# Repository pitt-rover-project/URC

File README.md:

# 🚀 University Rover Challenge - Pitt Robotics

> **Advanced Autonomous Rover System for University Rover Challenge**
> *ROS 2 • Python • Arduino • Docker • Computer Vision*

## 🎯 Project Overview

Complete software stack for the **University of Pittsburgh's University Rover Challenge (URC) Rover**. This system integrates advanced robotics technologies to compete in one of the most prestigious collegiate robotics competitions.

### 🏆 Competition Tasks
- **🚶 Autonomous Navigation** - GPS-guided traversal of challenging terrain
- **🎯 Equipment Servicing** - Precise manipulation tasks with robotic arm
- **📦 Extreme Delivery** - Package delivery in harsh environments
- **🔬 Science Operations** - Sample collection and analysis
- **🕹️ Teleoperation** - Manual control for complex scenarios

## ⚡ Quick Start

### 🐳 Docker Setup (Recommended)

**macOS Development:**
```bash
cd docker/local
chmod +x start_mac.sh
./start_mac.sh
```

**Jetson/Linux Deployment:**
```bash
cd docker/jetson
chmod +x start.sh
./start.sh
```

**Simulation Mode:**
```bash
cd docker/local
./sim-launch.sh
```

### 🤖 Launch Rover System

```bash
# Start main control interface
python3 -m guis.gen_gui

# Launch specific subsystems
python3 -m guis.arduino_gui      # Hardware communication
python3 -m guis.auto_gui         # Autonomous navigation
python3 -m guis.equip_serv_gui   # Equipment servicing
```

## 🏗️ System Architecture

### **Core Components**

```
🌐 ROS 2 Network Layer
├── 📡 Sensor Bridges (GPS, IMU, Cameras)
├── 🎮 Control Interfaces (Teleop, Autonomous)
├── 🤖 Hardware Abstraction (Motors, Servos)
└── 📊 Data Processing (Computer Vision, Navigation)

🖥️ GUI Control System
├── 🎛️ General Control Dashboard
├── 🚗 Motor Control Interface
├── 🧭 Navigation & Mapping
└── 📸 Camera Feed Management

🔧 Hardware Integration
├── ⚡ Arduino Communication
├── 📶 Serial Protocol Bridges
├── 🎯 Motor Control Systems
└── 📡 Sensor Data Acquisition
```

## 🛠️ Development Workflow

### **ROS 2 Development**

```bash
# Build ROS workspace
cd simulation/colcon_ws
colcon build

# Launch robot simulation
ros2 launch my_robot_description display.launch.py use_sim_time:=true

# Control with keyboard
ros2 run teleop_twist_keyboard teleop_twist_keyboard --ros-args -r /cmd_vel:=/teleop_cmd_vel

# Monitor system status
ros2 run rqt_console rqt_console
```

### **Git Workflow**
```bash
# Create feature branch
git fetch
git checkout -b feature/your-improvement

# Development cycle
git add .
git commit -m "feat: add autonomous navigation improvements"
git push origin feature/your-improvement

# Create pull request for review
```

## 📊 Technology Stack

### **🤖 Robotics & Control**
- **ROS 2 Humble** - Robot operating system
- **Gazebo** - Physics simulation environment
- **OpenCV** - Computer vision processing
- **PyQt5** - GUI framework for control interfaces

### **🔧 Hardware Integration**
- **Arduino** - Embedded sensor/actuator control
- **Serial Communication** - Hardware abstraction layer
- **NVIDIA Jetson** - Edge computing platform
- **GPS/IMU Sensors** - Navigation and localization

### **🚀 DevOps & Deployment**
- **Docker** - Containerized development environment
- **Docker Compose** - Multi-service orchestration
- **Make** - Build automation and cleanup

## 🎮 Competition Features

### **🧠 Autonomous Navigation**
- GPS-waypoint following
- Obstacle detection and avoidance
- Terrain analysis and path planning
- Real-time localization and mapping

### **🎯 Precision Control**
- Robotic arm manipulation
- Equipment servicing protocols
- Sample collection automation
- Fine motor control systems

### **📡 Communication Systems**
- Long-range telemetry
- Video streaming capabilities
- Emergency stop protocols
- Multi-operator interface support

## 📈 Performance Metrics

- **Navigation Accuracy**: ±2m GPS positioning
- **Video Latency**: <200ms streaming
- **Control Response**: <50ms command execution
- **Battery Life**: 4+ hours autonomous operation
- **Operating Range**: 1km+ radio communication

## 🔍 Diagnostics & Monitoring

```bash
# System health check
./ros2_quick_diagnostic.sh

# Network connectivity
./udp_connectivity_test.py

# Hardware status
python3 guis/gen_gui.py  # View sensor dashboard

# Log analysis
tail -f *.log
```

---

**Team**: University of Pittsburgh Robotics Club
**Status**: Active Development - 2025 Season

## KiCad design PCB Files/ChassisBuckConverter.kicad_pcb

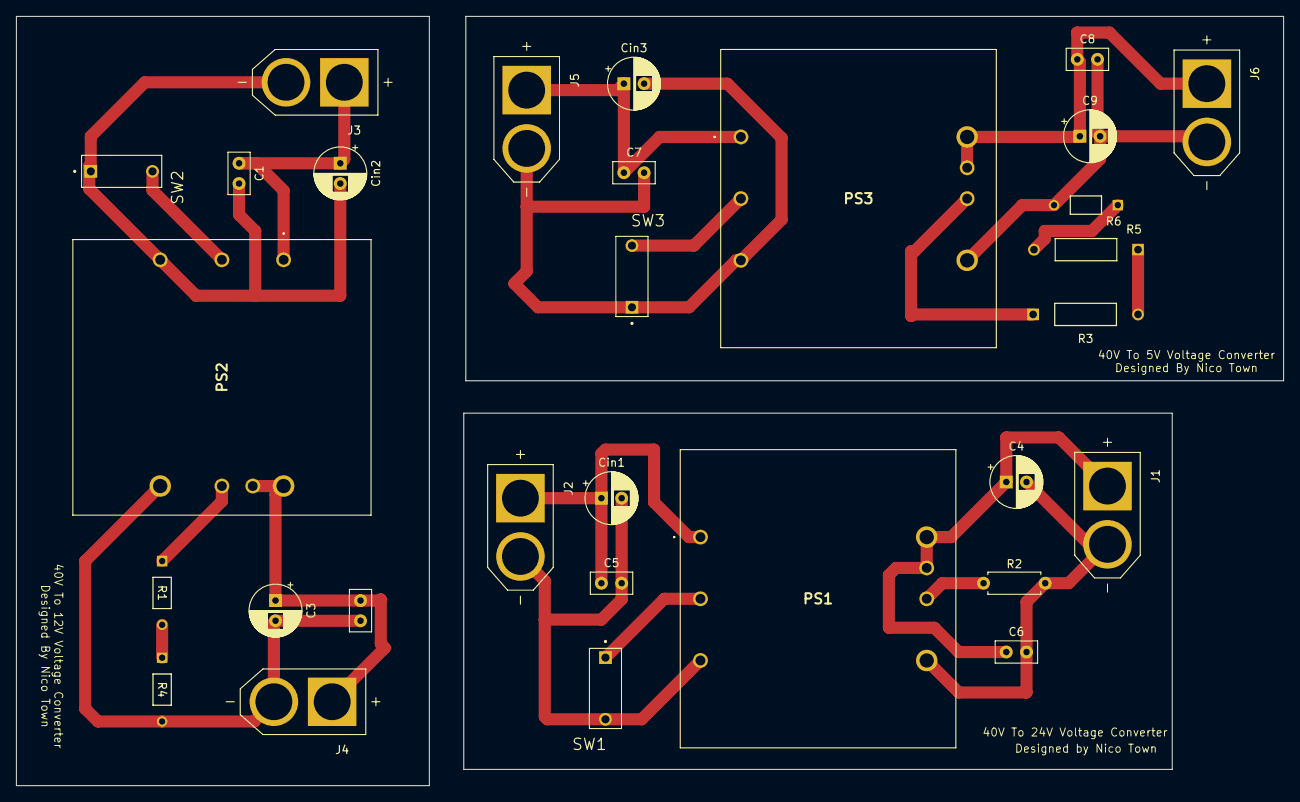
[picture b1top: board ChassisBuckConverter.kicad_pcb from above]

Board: 2 copper layers, 156.5 x 95.0 mm, 30 parts (0 on the bottom side), 21 nets.

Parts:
C1, C2, C5, C6, C7, C8: 22uF; C_Disc_D5.0mm_W2.5mm_P2.50mm
C3, C4, C9: 330uF; CP_Radial_D6.3mm_P2.50mm
Cin1, Cin2, Cin3: 330uF; CP_Radial_D6.3mm_P2.50mm
J1: 24V; AMASS_XT60-M
J2, J3, J5: 40V; AMASS_XT60-M
J4: 12V; AMASS_XT60-M
J6: 5V; AMASS_XT60-M
PS1, PS2, PS3: I7A48020A033V-0F1-R; I7A4W033A033V0F1R
R1: 1000; STA_CF18_STP
R2: 280; R_Axial_DIN0207_L6.3mm_D2.5mm_P7.62mm_Horizontal
R3: 8200; RES_CMF07_VIS
R4: 130; STA_CF18_STP
R5: 400; CMF55_VIS
R6: 180; STA_CF18_STP
SW1, SW2, SW3: SWITCH; SW_DS01-254-L-01BE

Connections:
unnamed: C4.2, C6.2, J1.N, PS1.4 (VOUT(-)), R2.2
unnamed: C4.1, C6.1, J1.P, PS1.7 (SENSE(+)), PS1.8 (VOUT(+))
unnamed: C5.1, Cin1.1, J2.P, PS1.1 (VIN(+))
unnamed: C5.2, Cin1.2, J2.N, PS1.3 (VIN(-)), SW1.1B
unnamed: C1.1, Cin2.1, J3.P, PS2.1 (VIN(+))
unnamed: C1.2, Cin2.2, J3.N, PS2.3 (VIN(-)), SW2.1A
unnamed: C2.2, C3.2, J4.N, PS2.4 (VOUT(-)), R4.2
unnamed: C2.1, C3.1, J4.P, PS2.7 (SENSE(+)), PS2.8 (VOUT(+))
unnamed: C7.1, Cin3.1, J5.P, PS3.1 (VIN(+))
unnamed: C7.2, Cin3.2, J5.N, PS3.3 (VIN(-)), SW3.1A
unnamed: C8.2, C9.2, J6.N, PS3.4 (VOUT(-)), R6.2
unnamed: C8.1, C9.1, J6.P, PS3.7 (SENSE(+)), PS3.8 (VOUT(+))
unnamed: PS1.2 (ON/OFF), SW1.1A
unnamed: PS1.6 (TRIM), R2.1
unnamed: PS2.2 (ON/OFF), SW2.1B
unnamed: PS2.6 (TRIM), R1.1
unnamed: PS3.2 (ON/OFF), SW3.1B
unnamed: PS3.6 (TRIM), R3.1
unnamed: R1.2, R4.1
unnamed: R3.2, R5.1
unnamed: R5.2, R6.1

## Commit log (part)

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2024-12-27 added current arduino code for gps, drive train, and ultrasonic sensors with their corresponding bridges
2024-12-27 fixed some issues with previous commit
2024-12-28 finished a basic docker set up
2024-12-28 combined the terminal publisher with the driver ros architecture
2024-12-31 start scripts
2024-12-31 subprocesses for the guis
2024-12-31 github cleanup
2025-01-09 updated port
2025-01-10 dockerfile fix
2025-01-10 updated pins
2025-01-10 ultrasonic fix
2025-01-13 docker readme
2025-01-13 better docker readme
2025-01-13 realsense for docker
2025-01-13 removed realsense
2025-01-13 docker attempt 2
2025-01-13 forgot -y
2025-01-13 docker attempt 3
2025-01-24 fixed a gui script
2025-01-25 docker attmpt 4
2025-01-25 docker compose
2025-01-25 commented out arduino for now
2025-01-25 removed acm0 for now
2025-01-25 privileged
2025-01-25 Created ime_demo arduino script
2025-01-25 docker for local
2025-01-27 added readme + fixed gui
2025-02-04 I say mama mia .py
2025-02-09 fixed some bridge code errors
2025-02-10 added teleop control to docker
2025-02-10 updated simulation
2025-02-10 deleted colcon_ws
2025-02-10 added colcon_ws to simulation
2025-02-10 removed colcon
2025-02-15 New files for simulation
2025-02-15 new motor stuff
2025-02-15 start up for the cameras
2025-02-15 Create Twist keyboard messages
2025-02-15 added distance between left and right wheels
2025-02-15 Making Gui code more Pythonic
2025-02-15 Added distance file
2025-02-15 Pushing branch to remote
2025-02-15 Adding the imu bridge
2025-02-17 Create Commands for Robot Subscriber
2025-02-18 Bridge work
2025-03-10 edited controls
2025-03-10 python3
2025-03-10 Fixing commented code - deletion
2025-03-10 Fixing even more! Commented out code.
2025-03-16 docker
2025-03-16 forgot an s
2025-03-16 Uploading progress on subscriber.py
2025-03-16 added a command
2025-03-16 Creating IMU Data Parser class that parses incoming message (from subscriber)
2025-03-16 Implementing feedback from Alexander's code review: "what the hell is the zip function? Use something simpler"
2025-03-22 testing 1st commit
2025-03-22 Added satellite parsing
2025-03-22 Added satellites parsing, changed distance prints, and motor serial
2025-04-07 Pushing latest work on subscribers - April 7th
2025-04-07 Connecting parsing interface with the subcriber hierarchy.
2025-04-08 Working on integrating GPS subscriber into the program. Fixing problems in arudino bridge base of missing motor code.
2025-04-12 mount drive into docker yaml
2025-04-12 camera file change
2025-04-12 Added more subscribers and teleop related matter. Fixed some spelling errors
2025-04-14 added hello.txt
2025-04-14 added hello.txt to branch alexiskwasinski
2025-04-14 reverting changes
2025-04-15 Fixed inaccurate baud rate. Back to 115200
2025-04-15 Resolving merge conflict - fixing error with version/volume keyword (volume accurate) in docker-compose.yml
2025-04-15 Resolving merge conflict.
2025-04-15 Working on integrating GPS subscriber into the program. Fixing problems in arudino bridge base of missing motor code.
    Resolving merge conflict...
2025-04-15 Resolving merge conflict
2025-04-19 Deleting build directory and adding instructions to README to run GUIs.
2025-04-19 changed the gui from rows/columns to cords and made it fullscreen
2025-06-02 Adding pycache to gitignore
2025-06-04 work on linking subscribers to gui
2025-06-17 Updates to docker/local documentation and testing subscribers in gui in local docker RLCPY [it works! I'm 90% sure]
2025-06-19 Improving docker/local ROS bash scripts. Beginning upgrades to the README to make spinning up a Docker container more accessible to the team.
2025-06-19 Improving README.md for docker/local repository
2025-06-27 moved imu code and updated motor code
2025-06-28 Adding: -app volume to jetson's docker - better instructors for local start_mac - improving *hopefully* communications between publishers and subscribers
2025-06-28 Improving README, deleting excess files, and adding Makefile to project root to help clean up project.
2025-06-28 Actually deleting unnecessary files
2025-06-29 Testing if alex is letting felipe and I git push -f main
2025-06-29 Setting everything back to normal
2025-07-14 added frame extraction for cameras
2025-07-18 Adding work on solving connection faults between base station and jetson
2025-07-18 troubleshooting gui changes
2025-07-21 Added frame_extract and changed frame_extract
2025-07-22 Finished camera_cv publishing and subcribing
2025-07-22 publishing and subscribing to the grayscale and depth image
2025-07-26 Adding troubleshooting code from Claude to gui branch - attempting to decipher connection issues with MacOS and Windows to the Ubuntu Jetson.
2025-07-30 got rid of unused imports
2025-07-30 gen_gui change
2025-07-31 Adding files to version control
2025-08-11 Buck Converter PCB Files
    Chassis Buck Converter From 40V down to 24V, 12V, or 5V.
2025-08-11 PCB Files Grouped
    Contains pcb files for buck converters that take voltage from 40V down to 24V, 12V, or 5V.
2025-08-11 Delete ChassisBuckConverter.kicad_pcb
    Deleting each of the files from my original commit.
2025-08-11 Delete ChassisBuckConverter.kicad_pro
    Deleting original commit.
2025-08-11 Delete ChassisBuckConverter.kicad_sch
    Final delete to original attempt.
2025-08-11 pcb files
    PCB files for three Buck Converters with voltages from 40V down to 24V, 12V, and 5V. Edited naming conventions to fit rest of repository.
2025-08-11 Delete PCB Files directory
    Fixing the name and this is the only way I know how right now.
2025-08-29 Pushing a *TON* of shell scripts
2025-08-29 Fixed local docker-compose issue
2025-08-29 Adding new gui structure
2025-09-05 changed pin numbers
2025-09-05 fixing up excess files and testing gui again
2025-09-07 trying to fix mac gui display issue with docker container compatability (x-forwarding)
2025-09-12 saved gray image
2025-09-12 fixed merge conflicts
2025-09-12 node
2025-09-12 some random gpt-5-mini code
2025-09-12 position
2025-09-12 vfds
2025-09-21 address PR comments
2025-09-21 Gui Enhancement (#38)
2025-09-21 added gps module folder and ino code for reading raw nmea data
2025-09-21 added gps module folder and ino code for reading raw nmea data (#39)
2025-09-21 fixed gen_gui and started to fix motor controls
2025-09-28 Implemented publisher in base station and subscriber in rover to receive motor control commands.
2025-09-28 fixed deceleration and made dark mode on main gui
2025-09-28 removed unnecessary files
2025-10-05 GUI updates (#43)
    * got rid of unused imports
    * gen_gui change
    * saved gray image
    * fixed merge conflicts
    * node
    * .
2025-10-05 added motor publisher to gui and fixed acceleration values in gui
2025-10-12 Fixing GUI not working on a MacBook
2025-10-12 Fixing GUI issues and arduino button not spinning up GUI/
2025-10-12 Motor publisher subscriber (#44)
    * Implemented publisher in base station and subscriber in rover to receive motor control commands.
    * added motor publisher to gui and fixed acceleration values in gui
    * Fixing GUI not working on a MacBook
    * Fixing GUI issues and arduino button not spinning up GUI/
    ---------
2025-10-12 serial connection to motor
2025-10-12 Revert "serial connection to motor"
    This reverts commit 8144bd8436e78eeb688e6f25c74955299cd3dfbf.
    THIS ISN"T WORKINGNGGG
2025-10-12 WORK
2025-10-12 Fixing excruciatingly slow transmit speeds
2025-10-19 Started object detection
2025-10-19 started autonomous routing
2025-11-02 debugging
2025-11-02 Motor publisher subscriber (#45)
    * Implemented publisher in base station and subscriber in rover to receive motor control commands.
    * added motor publisher to gui and fixed acceleration values in gui
    * Fixing GUI not working on a MacBook
    * Fixing GUI issues and arduino button not spinning up GUI/
    * serial connection to motor
    * serial connection to motor
2025-11-02 added docker run commands for camera
2025-11-02 added docker run commands for camera (#46)
2025-11-02 fixing docker command for camera
2025-11-02 Camera docker (#47)
2026-01-05 Update contributing guidelines to include branch convention and additional git commands
2026-01-05 Update contributing guidelines to include branch convention and additional git commands (#48)
2026-01-05 I say mama mia .py (#49)
2026-01-05 Documentation
2026-01-05 Add complete documentation table of contents for URC project
    - Introduced a comprehensive table of contents (TOC) for the URC Complete Documentation.
    - Organized sections covering project overview, system architecture, hardware requirements, software dependencies, Docker configuration, quick start guide, detailed startup procedures, ROS 2 architec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
    - Ensured all chapters and sections are properly linked for easy navigation.
2026-01-05 Update URC Complete Documentation: Adjust table of contents and improve formatting
    - Updated table of contents entries to reflect new page numbers for various sections.
    - Added headheight parameter to the document layout for better header spacing.
    - Defined YAML language for code listings to enhance readability.
    - Updated the PDF file to reflect the latest changes in the documentation.
2026-01-05 Users/n f9/docs (#50)
    * Documentation
    * Add complete documentation table of contents for URC project
    - Introduced a comprehensive table of contents (TOC) for the URC Complete Documentation.
    - Organized sections covering project overview, system architecture, hardware requirements, software dependencies, Docker configuration, quick start guide, detailed startup procedures, ROS 2 architec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
    - Ensured all chapters and sections are properly linked for easy navigation.
    * Update URC Complete Documentation: Adjust table of contents and improve formatting
2026-01-05 added documentation and final changes
2026-01-06 more changed to documentation to make it more accurate
2026-01-06 removed old file
2026-01-19 Documentation (#51)
    * added documentation and final changes
    * more changed to documentation to make it more accurate
    * removed old file
    ---------
